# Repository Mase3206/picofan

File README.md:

# picofan
Picofan is a Raspberry Pi Pico-based fan controller supporting PWM fans, speed measurement, and automatic speed adjustment. A RP2040-based PCB will be published in the future.

## Hardware Requirements

### Fans

Currenly, only PWM fans are supported due to their ease of digital control. Support for voltage-controlled fans may be implemented in the future.

picofan is fan voltage-agnostic by controlling fan power with individual transistors. <!-- TODO: add info about board vcc voltages when PCB and schematics are added to repo -->

### Temperature Sensors

Fan speed can be set to adjust automatically via a default or user-defined curve with feedback from one or more temperature sensors. Only analogue sensors are supported at this time, and they must be connected to a static serial shift register, such as the [Texas Instruments CD4021B](https://www.ti.com/product/CD4021B#pps). The RP2040 has four ADCs, three of which are available to the user on the Pico; one is reserved for the on-board temperature sensor.

### Control

picofan can be controlled by a Raspberry Pi 2 or later at the moment, but support for any device with a UART interface is planned. For my development, I am using a Raspberry Pi 3b. 

## Software

picofan has two software components:
1. Pico code, written in MicroPython
2. Companion device code, written in standard Python 3

The two devices communicate via a [custom protocol](./docs/protocol.md) over UART0 and use unique addresses to identify the command sender and recipient.

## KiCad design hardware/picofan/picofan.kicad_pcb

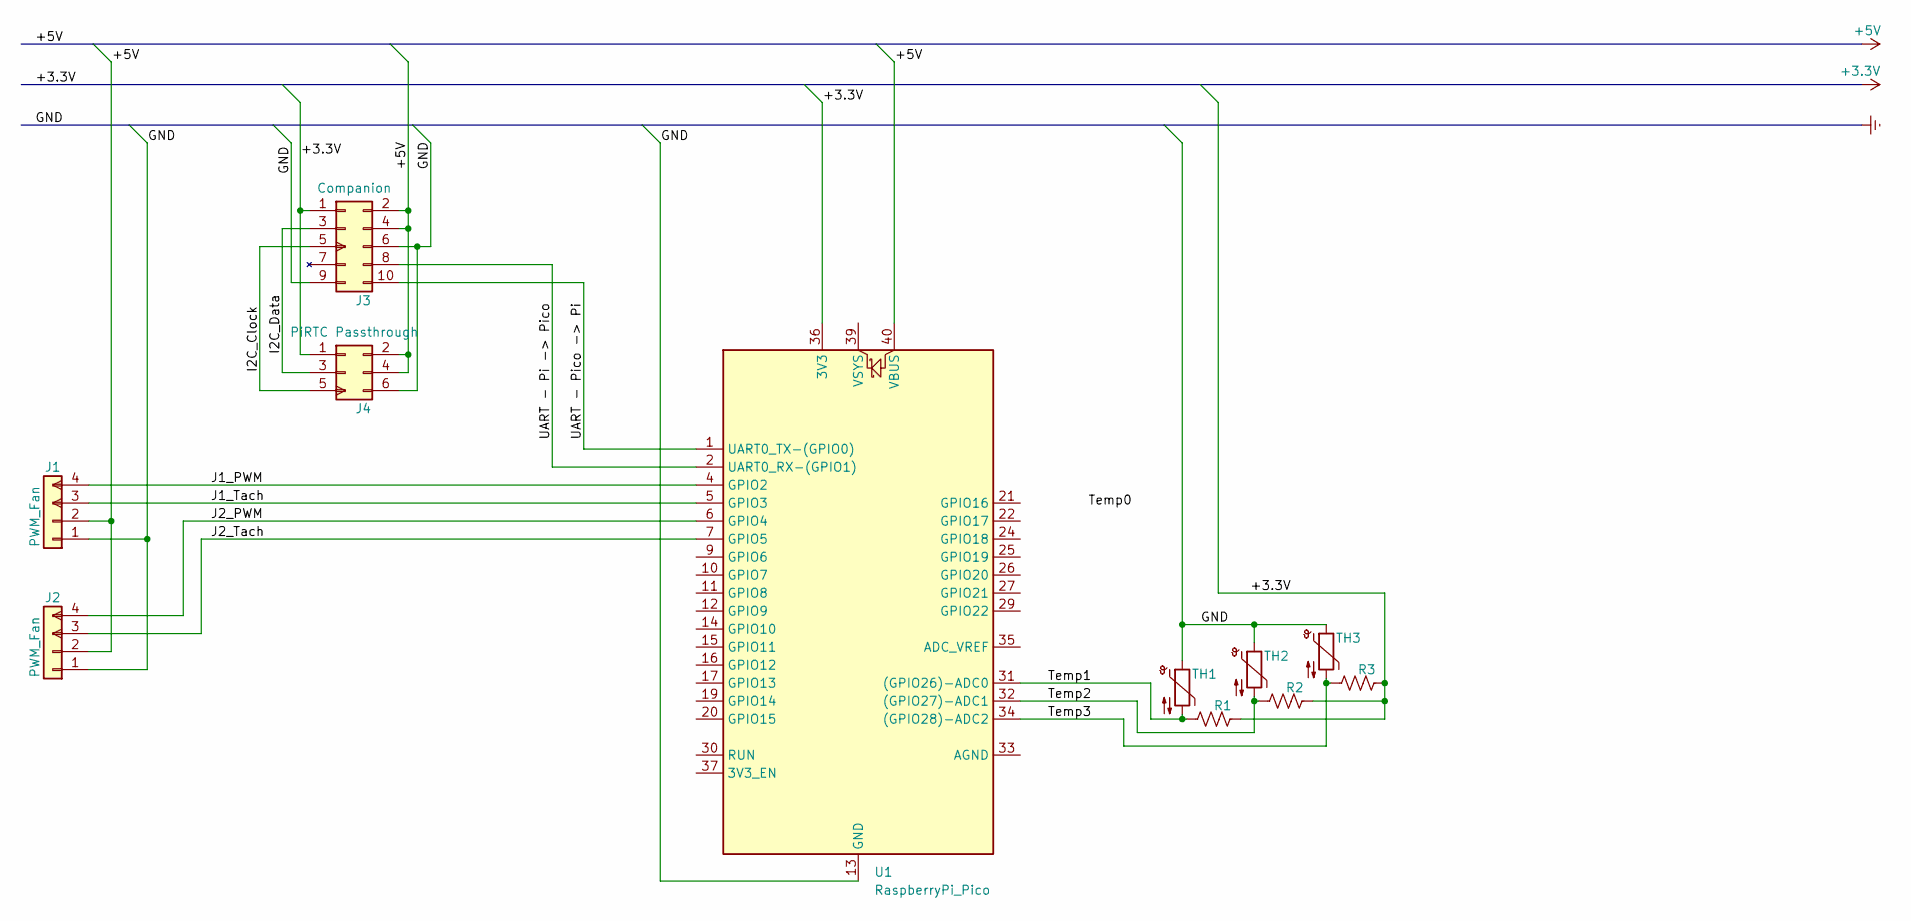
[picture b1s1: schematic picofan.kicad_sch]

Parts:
J1, J2: PWM_Fan; FanPinHeader_1x04_P2.54mm_Vertical
J3: Companion; IDC-Header_2x05_P2.54mm_Vertical
J4: PiRTC Passthrough; IDC-Header_2x03_P2.54mm_Vertical
R1, R2, R3: R_US; R_Axial_DIN0204_L3.6mm_D1.6mm_P5.08mm_Horizontal
TH1, TH2, TH3: Thermistor_NTC; R_Axial_DIN0204_L3.6mm_D1.6mm_P2.54mm_Vertical
U1: RaspberryPi_Pico; RaspberryPi_Pico_Common

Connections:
+3.3V: J3.1 (+3.3V), J4.1 (+3.3V), R1.2, R2.2, R3.2, U1.36 (3V3)
+5V: J1.2 (V_in), J2.2 (V_in), J3.2 (+5V), J3.4 (+5V), J4.2 (+5V), J4.4 (+5V), U1.40 (VBUS)
/I2C_Clock: J3.5 (I2C_Clk), J4.5 (I2C_Clk)
/I2C_Data: J3.3 (I2C_Data), J4.3 (I2C_Data)
/J1_PWM: J1.4 (PWM), U1.4 (GPIO2)
/J1_Tach: J1.3 (Tach), U1.5 (GPIO3)
/J2_PWM: J2.4 (PWM), U1.6 (GPIO4)
/J2_Tach: J2.3 (Tach), U1.7 (GPIO5)
/Temp1: R1.1, TH1.2, U1.31 ((GPIO26)-ADC0)
/Temp2: R2.1, TH2.2, U1.32 ((GPIO27)-ADC1)
/Temp3: R3.1, TH3.2, U1.34 ((GPIO28)-ADC2)
/UART - Pi -> Pico: J3.8 (UART_TX), U1.2 (UART0_RX-(GPIO1))
/UART - Pico -> Pi: J3.10 (UART_RX), U1.1 (UART0_TX-(GPIO0))
Earth: J1.1 (GND), J2.1 (GND), J3.6 (GND), J3.9 (GND), J4.6 (GND), TH1.1, TH2.1, TH3.1, U1.3 (GND), U1.8 (GND), U1.13 (GND), U1.18 (GND), U1.23 (GND), U1.28 (GND), U1.38 (GND)

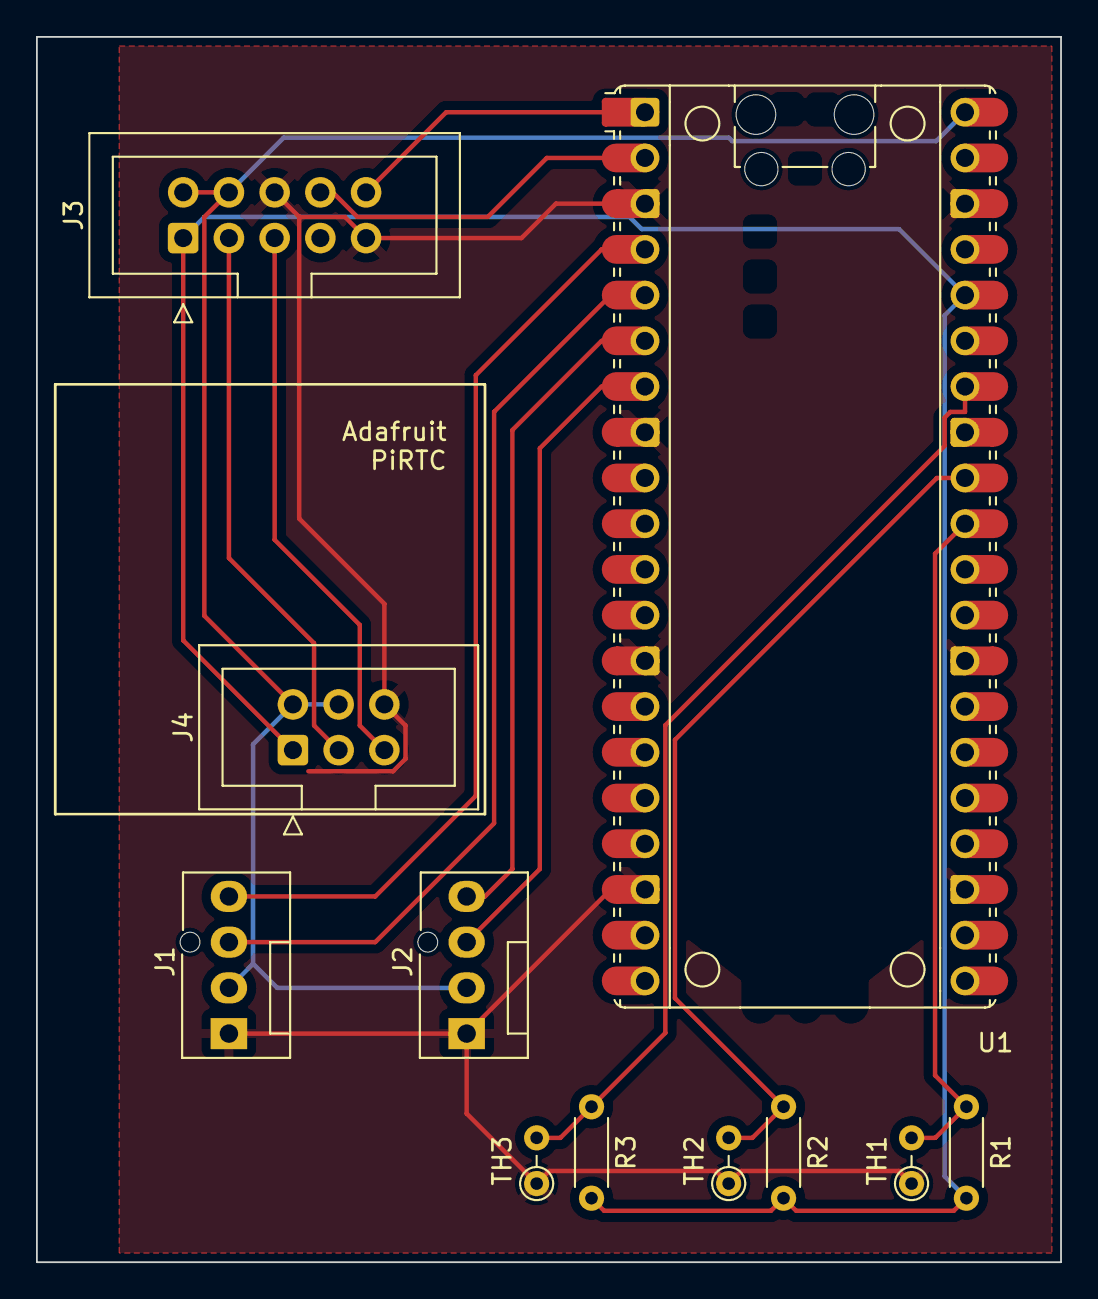
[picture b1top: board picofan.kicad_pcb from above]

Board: 2 copper layers, 56.9 x 68.1 mm, 11 parts (0 on the bottom side), 14 nets.

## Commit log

2024-01-05 move protocol.md into docs directory
2024-01-05 init code
2024-01-05 created Fan class
2024-01-05 i was writing the companion code, my bad
2024-01-06 update checksum protocol
2024-01-07 update protocol
2024-01-07 Clarify readme
2024-02-19 init micropython
2024-02-19 begin micropython
2025-06-24 create pcb
2025-06-24 switch to JSON for messages
2025-06-24 Implement main functionality and sensor integration for fan control
2025-06-24 moved code into two separate folders and poetry projects
2025-06-24 I think everything should be importing correctly in picofan?
2025-06-24 read and write null-terminated JSON over UART (needs to be implemented in pico side as well)
2025-06-25 objectify thermistor, fan, and fancurve
2025-06-25 switch to newline-terminated json
2025-06-25 add newline-terminated JSON uart wrapper
2025-06-25 uart irq
2025-06-25 pico-side command parsing
2025-06-25 add ruff
2025-06-25 refactoring
2025-06-25 linting
2025-06-25 add micropython cross-compiler and thonny (used to actually flash rp2), make picofan a micropico project
